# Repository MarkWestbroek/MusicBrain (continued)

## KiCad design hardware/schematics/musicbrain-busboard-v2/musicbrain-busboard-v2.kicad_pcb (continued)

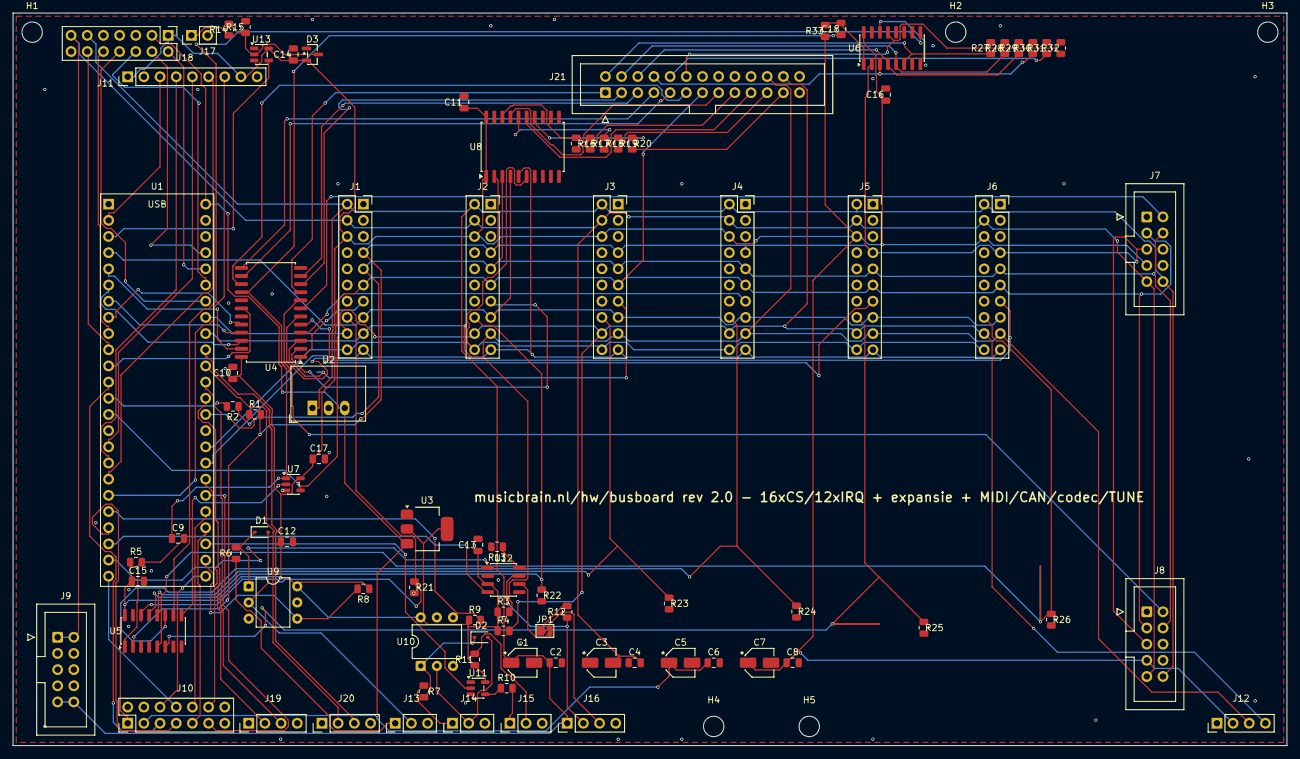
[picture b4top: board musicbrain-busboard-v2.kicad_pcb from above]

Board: 2 copper layers, 200.0 x 115.0 mm, 94 parts (0 on the bottom side), 105 nets.

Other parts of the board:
H1, H2, H3, H4, H5: M3; MountingHole_3.2mm_M3

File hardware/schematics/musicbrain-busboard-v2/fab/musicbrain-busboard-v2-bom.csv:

"Comment","Designator","Footprint","LCSC Part #"
"10u","C1,C3,C5,C7","CP_Elec_4x5.3",""
"100n","C2,C4,C6,C8,C10,C11,C12,C13,C14,C15,C16,C17","C_0805_2012Metric","C49678"
"220p","C9,C18","C_0805_2012Metric","C107145"
"1N4148WS","D1,D2","D_SOD-323",""
"BAT54S","D3","SOT-23","C7420333"
"SLOT 1","J1","PinSocket_2x10_P2.54mm_Vertical",""
"SLOT 2","J2","PinSocket_2x10_P2.54mm_Vertical",""
"SLOT 3","J3","PinSocket_2x10_P2.54mm_Vertical",""
"SLOT 4","J4","PinSocket_2x10_P2.54mm_Vertical",""
"SLOT 5","J5","PinSocket_2x10_P2.54mm_Vertical",""
"SLOT 6","J6","PinSocket_2x10_P2.54mm_Vertical",""
"HUB 1","J7","IDC-Header_2x05_P2.54mm_Vertical",""
"HUB 2","J8","IDC-Header_2x05_P2.54mm_Vertical",""
"PWR IN","J9","IDC-Header_2x05_P2.54mm_Vertical",""
"EXP","J10","PinHeader_2x07_P2.54mm_Vertical",""
"DISPLAY","J11","PinHeader_1x09_P2.54mm_Vertical",""
"QWIIC","J12","PinHeader_1x04_P2.54mm_Vertical",""
"MIDI IN1","J13","PinHeader_1x03_P2.54mm_Vertical",""
"MIDI IN2","J14","PinHeader_1x03_P2.54mm_Vertical",""
"MIDI OUT","J15","PinHeader_1x03_P2.54mm_Vertical",""
"CAN","J16","PinHeader_1x04_P2.54mm_Vertical",""
"AUDIO/CODEC","J17","PinHeader_2x07_P2.54mm_Vertical",""
"TUNE","J18","PinHeader_1x02_P2.54mm_Vertical",""
"DLG1 (Serial3)","J19","PinHeader_1x04_P2.54mm_Vertical",""
"DLG2 (Serial4)","J20","PinHeader_1x04_P2.54mm_Vertical",""
"EXPANSION","J21","IDC-Header_2x13_P2.54mm_Vertical",""
"TERM","JP1","SolderJumper-2_P1.3mm_Open_TrianglePad1.0x1.5mm",""
"33R","R1,R2,R11,R16,R17,R18,R19,R20","R_0805_2012Metric",""
"2k2","R3,R4","R_0805_2012Metric",""
"10k","R5,R13,R33","R_0805_2012Metric","C17414"
"220R","R6,R7","R_0805_2012Metric",""
"1k","R8,R9","R_0805_2012Metric","C17513"
"10R","R10","R_0805_2012Metric",""
"120R","R12","R_0805_2012Metric",""
"100k","R14,R15,R21,R22,R23,R24,R25,R26,R27,R28,R29,R30,R31,R32","R_0805_2012Metric","C149504"
"Teensy 4.1","U1","",""
"R-78E5.0-0.5","U2","Converter_DCDC_RECOM_R-78E-0.5_THT",""
"AMS1117-3.3","U3","SOT-223-3_TabPin2",""
"74HC154","U4","SOIC-24W_7.5x15.4mm_P1.27mm",""
"74HC165","U5,U6","SOIC-16_3.9x9.9mm_P1.27mm","C5613"
"74LVC1G125","U7","SOT-23-5","C12518"
"74LVC245","U8","SOIC-20W_7.5x12.8mm_P1.27mm",""
"H11L1","U9,U10","DIP-6_W7.62mm",""
"74LVC1G17","U11,U13","SOT-23-5",""
"SN65HVD230","U12","SOIC-8_3.9x4.9mm_P1.27mm",""

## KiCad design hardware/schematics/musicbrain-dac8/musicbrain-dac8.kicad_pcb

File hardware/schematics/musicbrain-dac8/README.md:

# MusicBrain DAC8 — 8× CV-uitgang (slotkaart)

**Praktisch:** acht CV-uitgangen. Hiermee stuurt de software analoge
modules aan: sequenties, LFO's, envelopes of random spanningen naar
elke Eurorack-ingang, sample-synchroon over alle kanalen (LDAC).
Combineer met een jack8 als front.

**Status**: rev 2.0 — ERC 0, netlijst pad-voor-pad geverifieerd, DRC 0/0.
**Spec**: `doc/spi-bus-spec.md` v2.0. Bord **60 × 45 mm**, 2 lagen.

## Gen 2 (rev 2.0, 2026-07-16)

- Slot **2×12**; H 80 → 45; DACs onder hun CV-kolommen (U1 → CV1–4,
  U2 → CV5–8). Daisy-chain, LDAC-buslijn en J2-contract ongewijzigd.
- DGND-reddingsspoor (pin 15) vast in de generator; koper via freerouting.

De schakelingbeschrijving hieronder is ongewijzigd; waar de lopende
tekst nog gen-1-maten of 2×10 noemt, geldt bovenstaande. Overzicht en
pinouts hieronder zijn gen-2-gegenereerd.

## Wat het is

8 nette CV-uitgangen uit **2× AD5754BREZ** (16-bit quad-DAC, ±10V-bereik)
met een gedeelde **ADR421**-referentie (2,5 V precisie) — hetzelfde
gevalideerde recept als de AD5754-breakout, nu als slotkaart in lijn met
GATE8/ADC8.

## Architectuur

- **Daisy-chain**: MOSI → U1.SDIN, U1.SDO → U2.SDIN, U2.SDO → MISO.
  Eén CS voor beide chips; de firmware klokt 48-bit frames (2×24) en
  bereikt beide DAC's in één transactie. U2.SDO is tri-state bij CS hoog.
- **LDAC = buslijn** (slotpin 15): beide chips laden hun uitgangsregisters
  tegelijk op LDAC↓ — en tegelijk met álle andere DAC-kaarten op de bus.
  Dat is precies waarvoor de LDAC-lijn in de spec bestaat.
- **Offset binary** (BIN/2sCOMP = pin 5 → +3V3), ~CLR (pin 11) met 10k
  pull-up (R1), DVCC (pin 14) = +3V3, DGND (pin 15) = GND, interne
  versterkers op ±12V (AVDD/AVSS), EP-pads aan AVSS.
- **~LDAC = pin 10** → de bus-LDAC-lijn (slotpin 15); pin 12/13 = NC.
  De AD5754-pinnummering is geverifieerd tegen de datasheet
  (`doc/data-sheets/AD5754BREZ data.md`), Nic Newdigate's ontwerp én het
  ComponentSearchEngine-symbool — drie onafhankelijke bronnen.
- **AD5754BREZ heeft géén interne referentie** (de "R" in de datasheet-titel
  slaat op de R-variant die dat wél heeft). Vandaar de **ADR421** (U3, 2,5 V
  precisie) → REFIN (pin 17) van beide chips, met **0,1 µF (C6) + 10 µF (C14)**
  ontkoppeling op VREF zoals de datasheet voorschrijft.
- 100 Ω serie per uitgang (R2–R9), kortsluitbescherming.

## Kanaaltoewijzing

| CV | DAC | | CV | DAC |
|---|---|---|---|---|
| CV1 | U1·B | | CV5 | U2·A |
| CV2 | U1·A | | CV6 | U2·B |
| CV3 | U1·C | | CV7 | U2·C |
| CV4 | U1·D | | CV8 | U2·D |

(CV1/CV2 verwisseld t.o.v. alfabetisch — routinggedreven; firmware-tabel.)

## Aansluitingen

- **J1** (haakse male 2×10, onderrand): volledig contract incl. +12V,
  −12V, +3V3, LDAC; MOSI én MISO in gebruik (daisy).
- **J2** (haakse male 1×10, bovenrand): 1 = GND, 2–9 = CV1..8, 10 = GND —
  zelfde jack8-contract; **JP1 op het jack8-printje OPEN laten** (outputs!).

## PCB-notities

De acht VOUT's verlaten de chips via korte F-escapes naar via's en lopen
als B.Cu-lanes (y 114,3–118,3, strikt genest) naar de serieweerstandsrij.
De stuursignalen dalen als B-rijen onderin (CS 168,6 / SCLK 169,4 /
MOSI 170,2 / CLR 162,4) naar F-verticalen die de 0,65 mm-westkolommen
in nesten ("diepste entry → oostelijkste verticaal"); LDAC heeft een
F-band op y 167,3 en stapt bij U1 van onderen de padkolom in. De
±12V/+3V3-verdeling loopt via een F-corridor (y 120,3/121,1) boven de
chips en B-banden (y 160,8/161,6) onderlangs. VREF loopt op B.Cu van de
ADR421 naar beide REFIN-pinnen. DGND-pads tussen de fijne entries hangen
aan eigen redding-via's.

## Firmware

Setup per chip (via de keten): power-up register (alle kanalen aan),
output range ±10V, BIN-coding. Daarna per sample: 2×24 bit data door de
keten schuiven, CS hoog, en LDAC↓ (buslijn) voor de synchrone update.

## Aansluitoverzicht

### Pinouts

Bovenaanzicht van het bord (kijkend op de pinnen); pin 1 = vierkant. Gegenereerd uit het bordbestand met `hardware/kicad-generators/pinout_svg.py`.

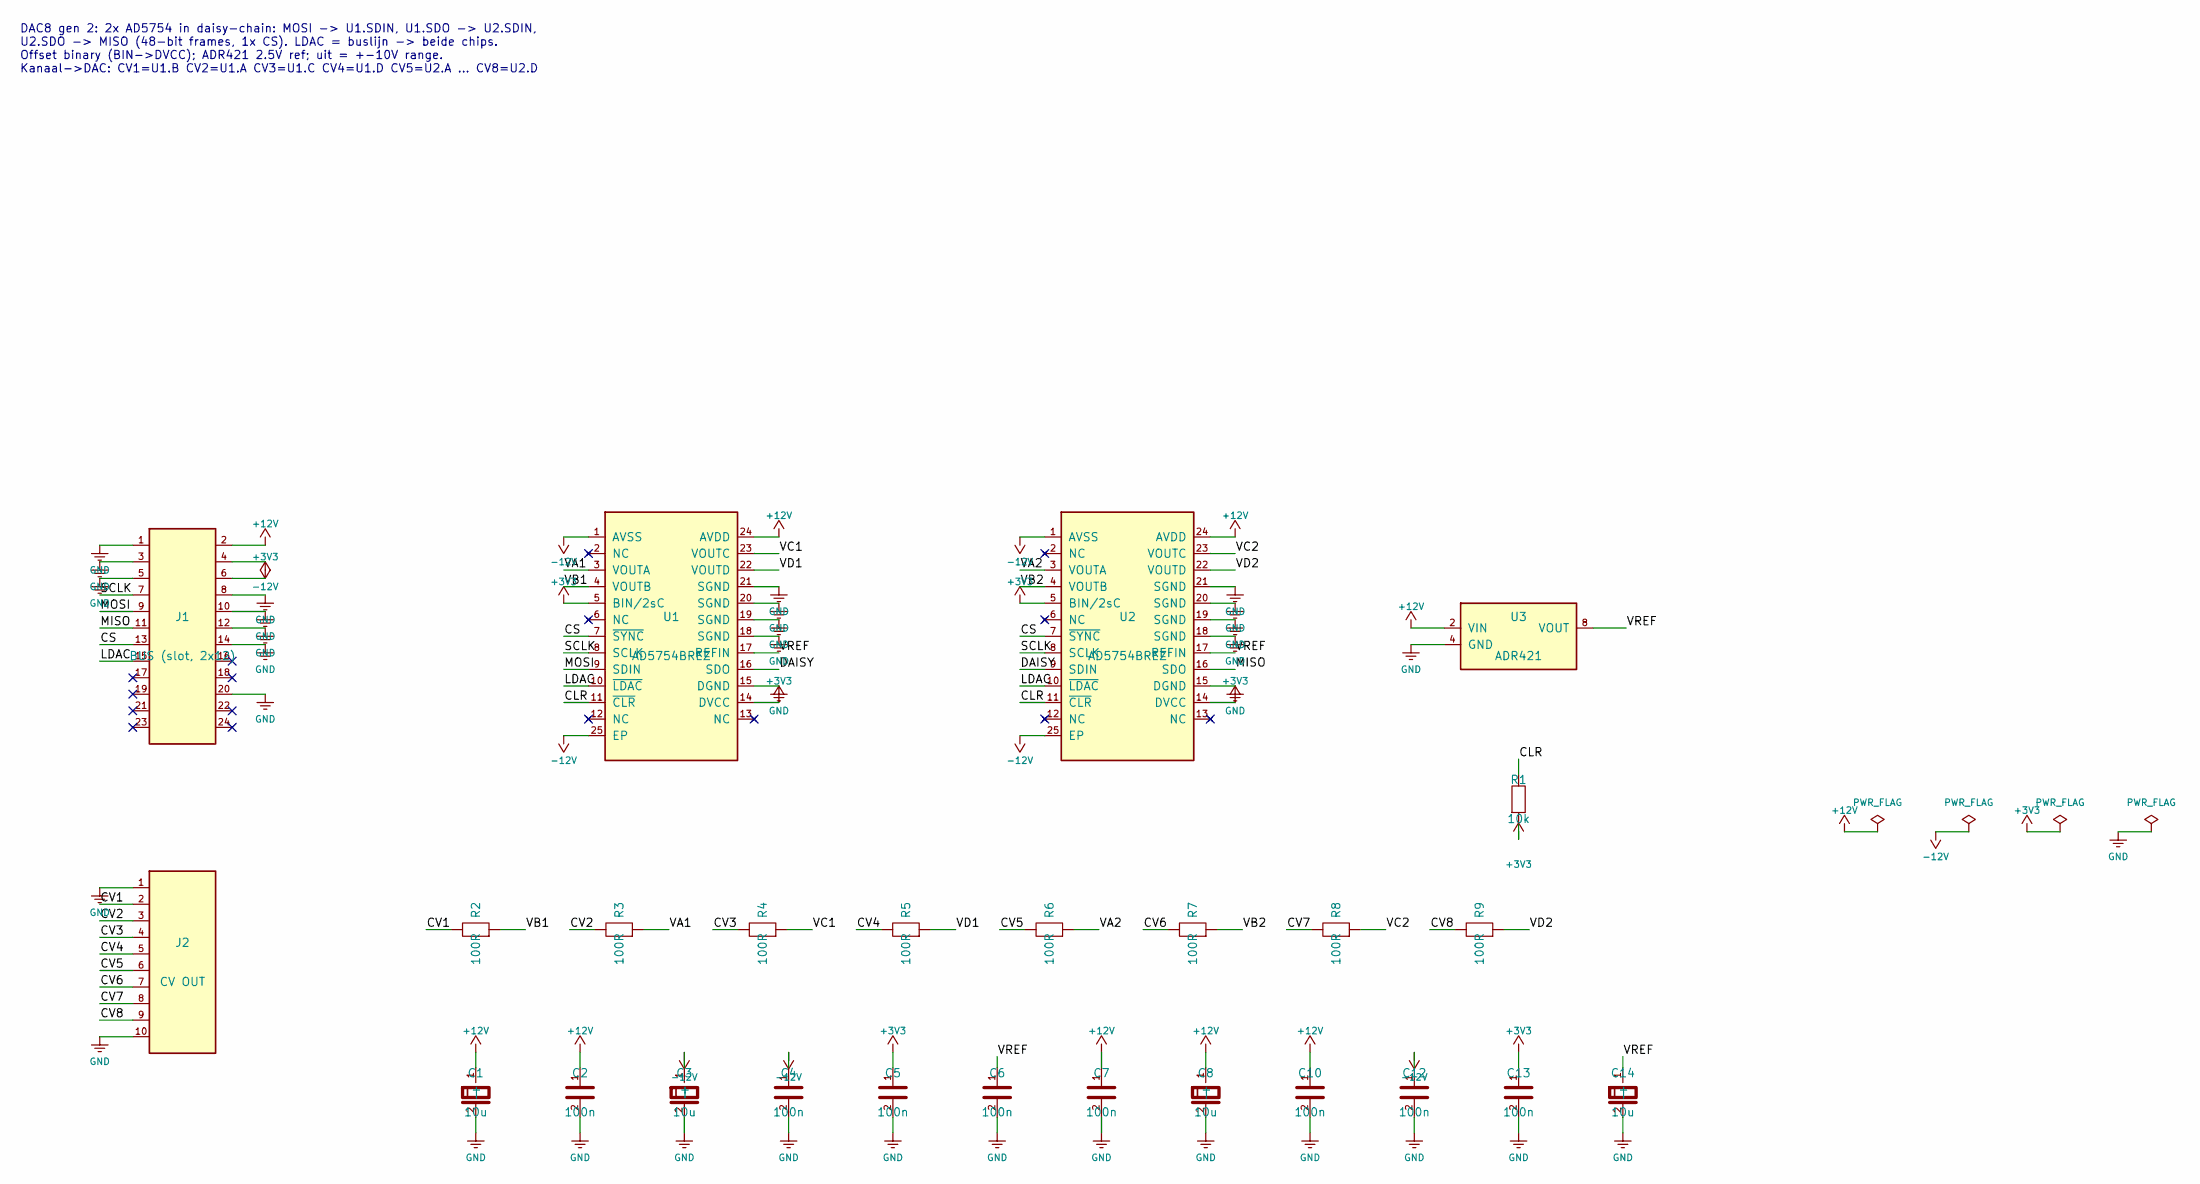
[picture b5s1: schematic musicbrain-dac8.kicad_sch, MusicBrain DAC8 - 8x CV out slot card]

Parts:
C1, C3, C8, C14: 10u; CP_Elec_4x5.3
C2, C4, C5, C6, C7, C10, C12, C13: 100n; C_0805_2012Metric
J1: BUS (slot, 2x12); PinHeader_2x12_P2.54mm_Horizontal
J2: CV OUT; PinHeader_1x10_P2.54mm_Horizontal
R1: 10k; R_0805_2012Metric
R2, R3, R4, R5, R6, R7, R8, R9: 100R; R_0805_2012Metric
U1, U2: AD5754BREZ; HTSSOP-24-1EP_4.4x7.8mm_P0.65mm_EP3.2x5mm
U3: ADR421; SOIC-8_3.9x4.9mm_P1.27mm

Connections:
+3V3: C5.1, C13.1, J1.6, R1.2, U1.5 (BIN/2sC), U1.14 (DVCC), U2.5 (BIN/2sC), U2.14 (DVCC)
+12V: C1.1 (+), C2.1, C7.1, C8.1 (+), C10.1, J1.2, U1.24 (AVDD), U2.24 (AVDD), U3.2 (VIN)
-12V: C3.1 (+), C4.1, C12.1, J1.4, U1.1 (AVSS), U1.25 (EP), U2.1 (AVSS), U2.25 (EP)
/CLR: R1.1, U1.11 (~CLR), U2.11 (~CLR)
/CS: J1.13, U1.7 (~SYNC), U2.7 (~SYNC)
/CV1: J2.2, R2.1
/CV2: J2.3, R3.1
/CV3: J2.4, R4.1
/CV4: J2.5, R5.1
/CV5: J2.6, R6.1
/CV6: J2.7, R7.1
/CV7: J2.8, R8.1
/CV8: J2.9, R9.1
/DAISY: U1.16 (SDO), U2.9 (SDIN)
/LDAC: J1.15, U1.10 (~LDAC), U2.10 (~LDAC)
/MISO: J1.11, U2.16 (SDO)
/MOSI: J1.9, U1.9 (SDIN)
/SCLK: J1.7, U1.8 (SCLK), U2.8 (SCLK)
/VA1: R3.2, U1.3 (VOUTA)
/VA2: R6.2, U2.3 (VOUTA)
/VB1: R2.2, U1.4 (VOUTB)
/VB2: R7.2, U2.4 (VOUTB)
/VC1: R4.2, U1.23 (VOUTC)
/VC2: R8.2, U2.23 (VOUTC)
/VD1: R5.2, U1.22 (VOUTD)
/VD2: R9.2, U2.22 (VOUTD)
/VREF: C6.1, C14.1 (+), U1.17 (REFIN), U2.17 (REFIN), U3.8 (VOUT)
GND: C1.2 (-), C2.2, C3.2 (-), C4.2, C5.2, C6.2, C7.2, C8.2 (-), C10.2, C12.2, C13.2, C14.2 (-), J1.1, J1.3, J1.5, J1.8, J1.10, J1.12, J1.14, J1.20, J2.1, J2.10, U1.15 (DGND), U1.18 (SGND), U1.19 (SGND), U1.20 (SGND), U1.21 (SGND), U2.15 (DGND), U2.18 (SGND), U2.19 (SGND), U2.20 (SGND), U2.21 (SGND), U3.4 (GND)

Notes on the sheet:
DAC8 gen 2: 2x AD5754 in daisy-chain: MOSI -> U1.SDIN, U1.SDO -> U2.SDIN, U2.SDO -> MISO (48-bit frames, 1x CS). LDAC = buslijn -> beide chips. Offset binary (BIN->DVCC); ADR421 2.5V ref; uit = +-10V range. Kanaal->DAC: CV1=U1.B CV2=U1.A CV3=U1.C CV4=U1.D CV5=U2.A ... CV8=U2.D

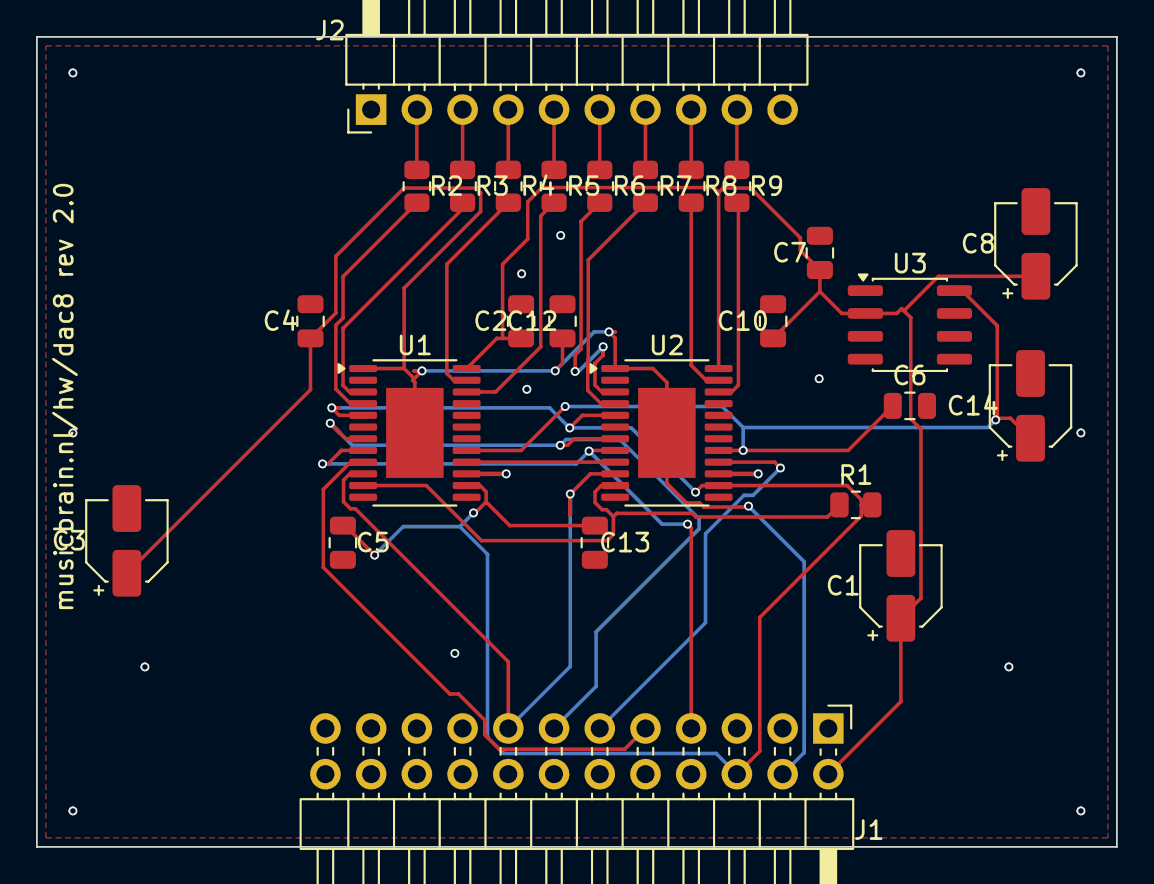
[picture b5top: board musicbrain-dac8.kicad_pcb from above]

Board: 2 copper layers, 60.0 x 45.0 mm, 26 parts (0 on the bottom side), 28 nets.

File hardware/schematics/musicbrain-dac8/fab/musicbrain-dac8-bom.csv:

"Comment","Designator","Footprint","LCSC Part #"
"10u","C1,C3,C8,C14","CP_Elec_4x5.3","C3343"
"100n","C2,C4,C5,C6,C7,C10,C12,C13","C_0805_2012Metric","C49678"
"BUS","J1","PinHeader_2x10_P2.54mm_Horizontal","C19190505"
"CV OUT","J2","PinHeader_1x10_P2.54mm_Horizontal","C2687688"
"10k","R1","R_0805_2012Metric","C17414"
"100R","R2,R3,R4,R5,R6,R7,R8,R9","R_0805_2012Metric","C17408"
"AD5754BREZ","U1,U2","HTSSOP-24-1EP_4.4x7.8mm_P0.65mm_EP3.2x5mm","C650230"
"ADR421","U3","SOIC-8_3.9x4.9mm_P1.27mm","C29739"
